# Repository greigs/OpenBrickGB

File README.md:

[For more info visit the hackaday writeup](https://hackaday.io/project/204088-lego-game-boy-functional-upgrade)

### Directory overview

- 3D Printed Parts: STL files for custom spacers and assemblies used inside the LEGO shell.
- Bill of Materials: CSVs listing components for the main PCB, button PCBs, and other parts.
- ButtonBoard PCBs: KiCad project assets and Gerbers for the button and D‑pad PCBs.
- Datasheets: Reference PDFs for key components (LCD, charger, amp, logic, regulators, etc.).
- Main PCB: KiCad project, fabrication outputs (Gerbers/DRLs), and pick‑and‑place (CPL) for the main board.
- Reference 3D Models: OBJ files used for fit checks and visualization of assemblies.
- Reference Bricklink Studio Designs: BrickLink Studio `.io` design files and a reference image for the LEGO build.

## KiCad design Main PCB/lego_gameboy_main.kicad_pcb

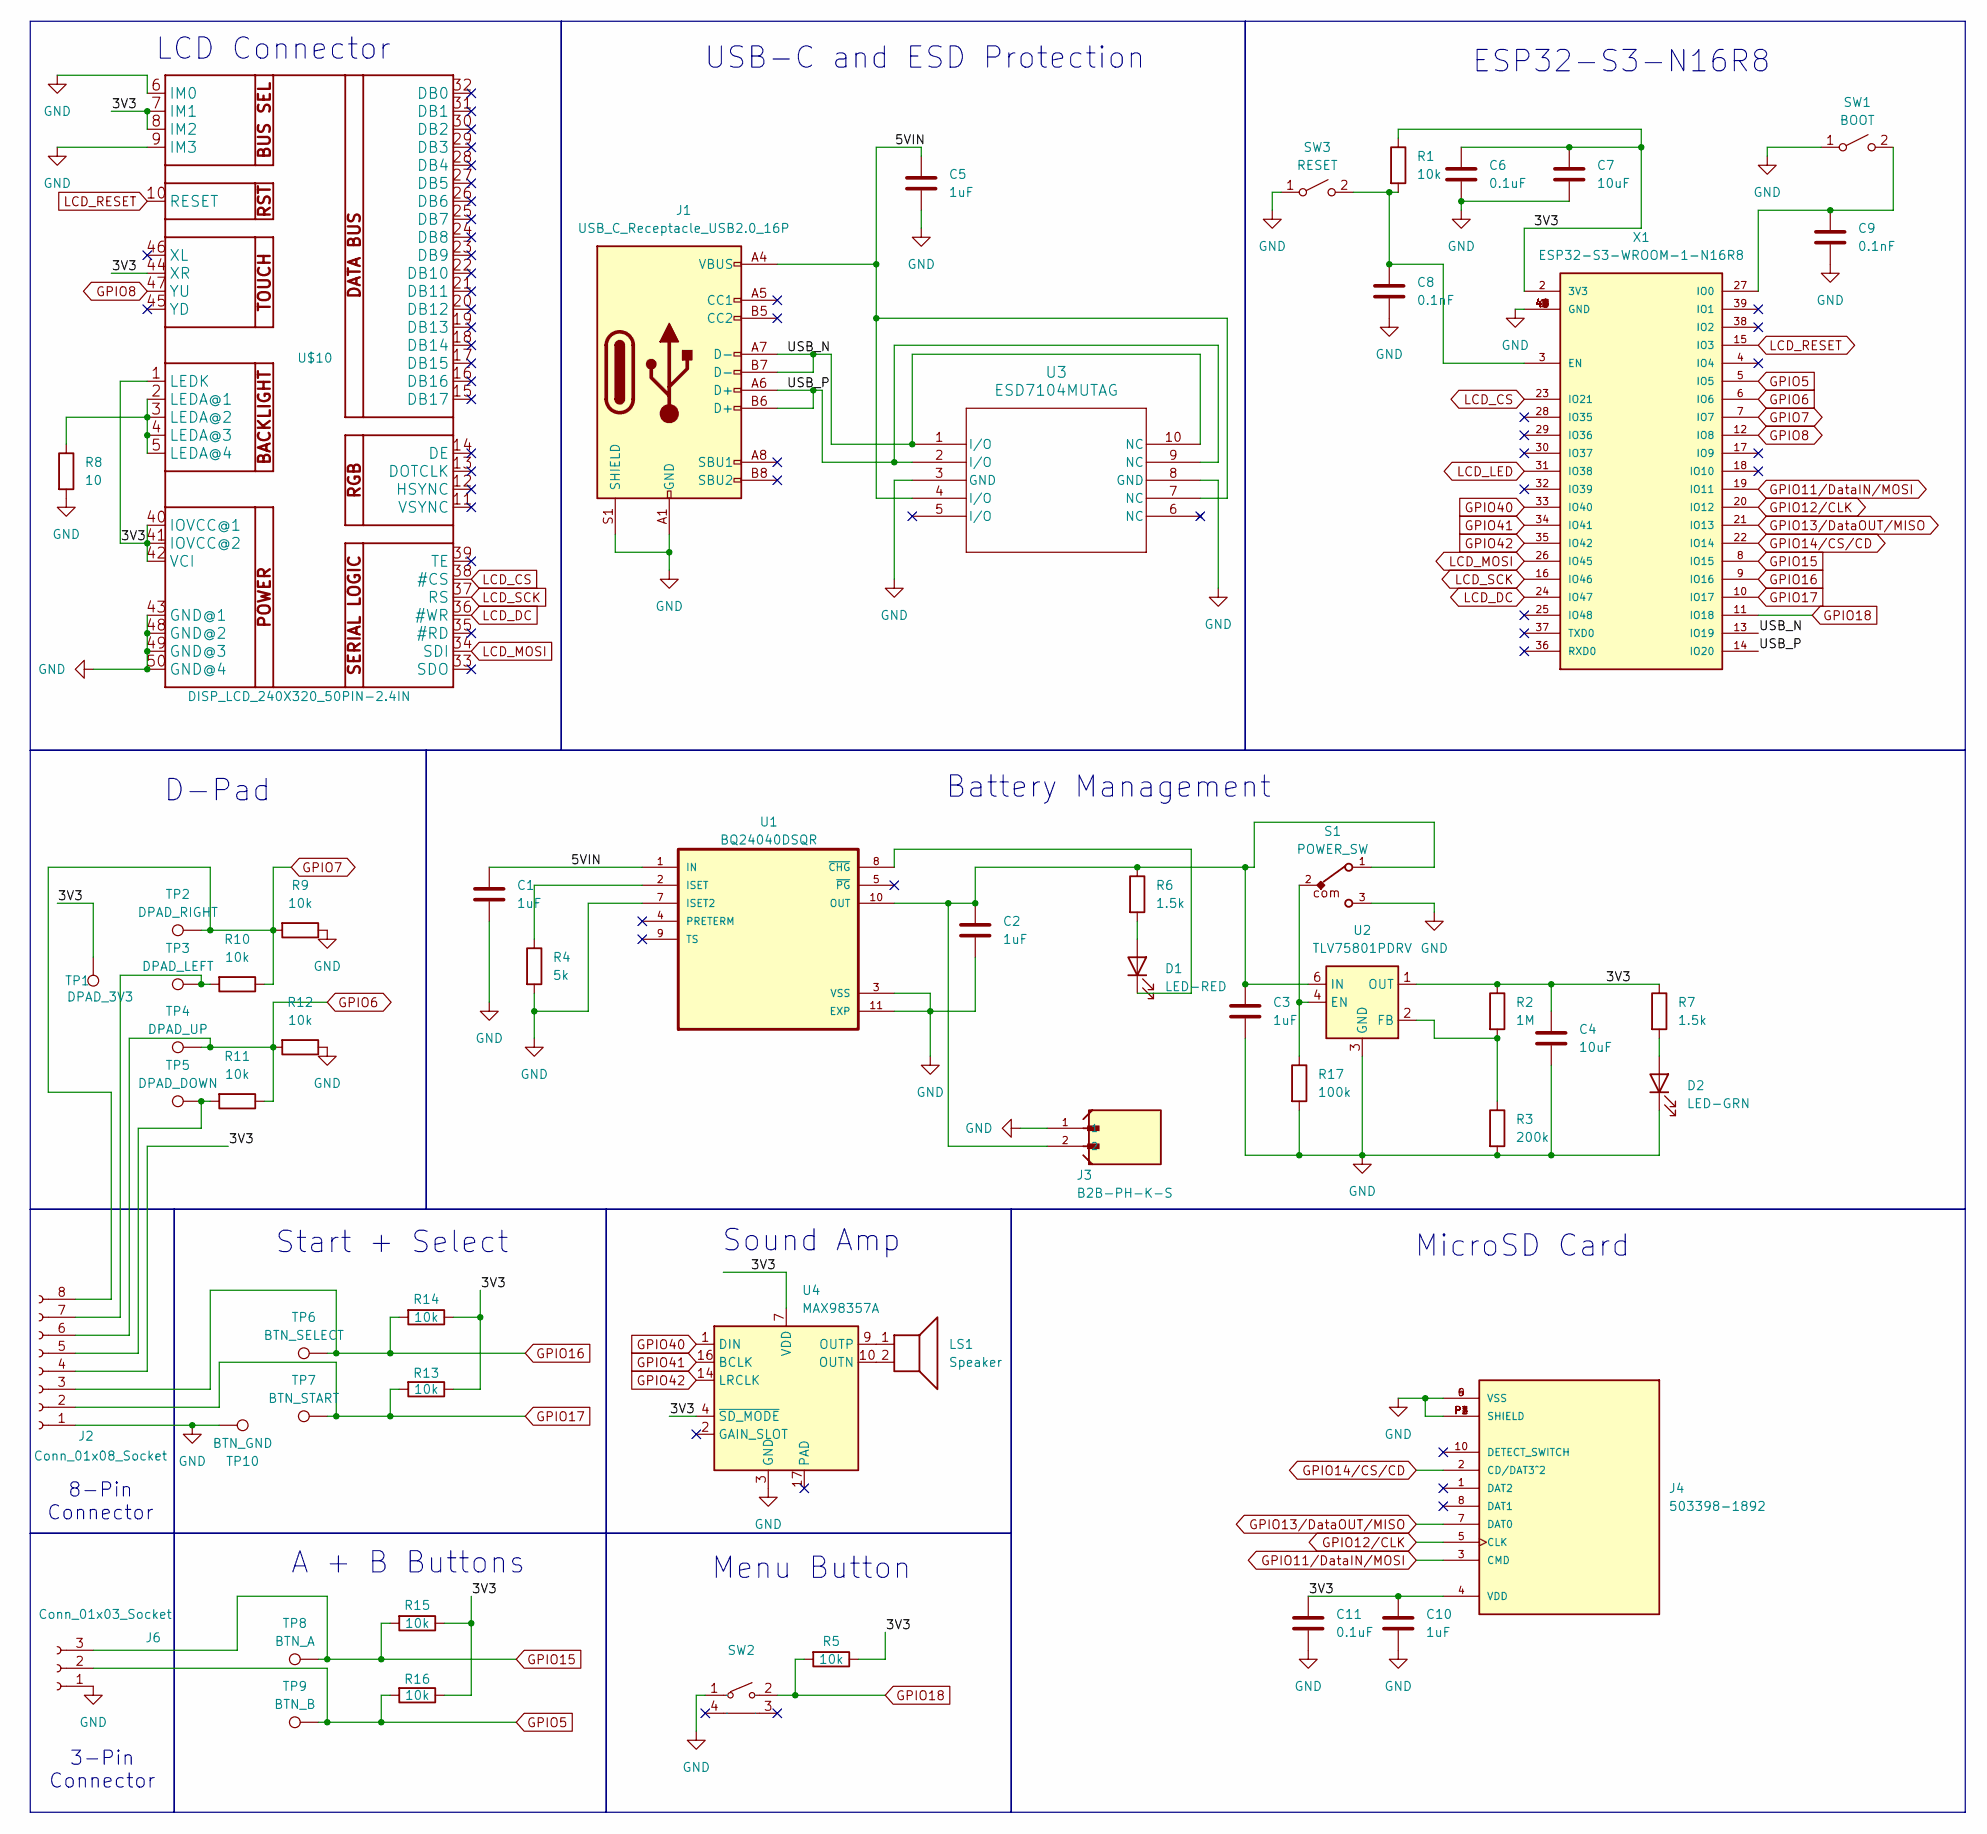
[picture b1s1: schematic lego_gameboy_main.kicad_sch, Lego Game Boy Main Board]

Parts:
C1, C2, C3, C5, C10: 1uF; C_0603_1608Metric
C4, C7: 10uF; C_0603_1608Metric
C6, C11: 0.1uF; C_0603_1608Metric
C8, C9: 0.1nF; C_0603_1608Metric
D1: LED-RED; LED_0603_1608Metric
D2: LED-GRN; LED_0603_1608Metric
J1: USB_C_Receptacle_USB2.0_16P; USB_C_Receptacle_G-Switch_GT-USB-7025
J2: Conn_01x08_Socket; JST_SUR_BM08B-SURS-TF_1x08-1MP_P0.80mm_Vertical
J3: B2B-PH-K-S; JST_PH_S2B-PH-K_1x02_P2.00mm_Horizontal
J4: 503398-1892; MOLEX_503398-1892; PARTREV 0; DigiKey_Part_Number WM11190CT-ND
J6: Conn_01x03_Socket; JST_SUR_BM03B-SURS-TF_1x03-1MP_P0.80mm_Vertical
LS1: Speaker; Speaker_CUI_CMR-1206S-67
R1, R5, R9, R10, R11, R12, R13, R14, R15, R16: 10k; R_0603_1608Metric
R2: 1M; R_0603_1608Metric
R3: 200k; R_0603_1608Metric
R4: 5k; R_0603_1608Metric
R6, R7: 1.5k; R_0603_1608Metric
R8: 10; R_0603_1608Metric
R17: 100k; R_0603_1608Metric
S1: POWER_SW; 450404015514
SW1: BOOT; SW_TS-1088-AR02016
SW2: SW-SMD_GT-TC185B-H038-L1; Manufacturer Part GT-TC185B-H038-L1; LCSC Part Name 4.9*5.5*3.8mm 卧贴 轻触开关
SW3: RESET; SW_TS-1088-AR02016
TP1: DPAD_3V3; TestPoint_Pad_D1.0mm
TP2: DPAD_RIGHT; TestPoint_Pad_D1.0mm
TP3: DPAD_LEFT; TestPoint_Pad_D1.0mm
TP4: DPAD_UP; TestPoint_Pad_D1.0mm
TP5: DPAD_DOWN; TestPoint_Pad_D1.0mm
TP6: BTN_SELECT; TestPoint_Pad_D1.0mm
TP7: BTN_START; TestPoint_Pad_D1.0mm
TP8: BTN_A; TestPoint_Pad_D1.0mm
TP9: BTN_B; TestPoint_Pad_D1.0mm
TP10: BTN_GND; TestPoint_Pad_D1.0mm
U1: BQ24040DSQR; SON40P200X200X80-11N
U2: TLV75801PDRV; WSON-6-1EP_2x2mm_P0.65mm_EP1x1.6mm
U3: ESD7104MUTAG; UDFN10_ONS
U4: MAX98357A; TQFN-16-1EP_3x3mm_P0.5mm_EP1.23x1.23mm
U$10: DISP_LCD_240X320_50PIN-2.4IN; TFT_2.4IN_240X320_50PIN
X1: ESP32-S3-WROOM-1-N16R8; ESP32S3WROOM1N8R2; MANUFACTURER_PART_NUMBER ESP32-S3-WROOM-1-N16R8

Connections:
/3V3: C4.1, C6.1, C7.1, C10.1, C11.1, J2.4, J4.4 (VDD), R1.1, R2.1, R5.1, R7.1, R13.1, R14.1, R15.1, R16.1, TP1.1, U2.1 (OUT), U4.4 (~SD_MODE), U4.7 (VDD), U4.8 (VDD), U$10.1 (LEDK), U$10.7 (IM1), U$10.8 (IM2), U$10.40 (IOVCC@1), U$10.41 (IOVCC@2), U$10.42 (VCI), U$10.44 (XR), X1.2 (3V3)
/5VIN: C1.1, C5.1, J1.A4 (VBUS), J1.A9 (VBUS), J1.B4 (VBUS), J1.B9 (VBUS), U1.1 (IN), U3.4 (I/O), U3.7 (NC)
/USB_N: J1.A7 (D-), J1.B7 (D-), U3.1 (I/O), U3.10 (NC), X1.13 (IO19)
/USB_P: J1.A6 (D+), J1.B6 (D+), U3.2 (I/O), U3.9 (NC), X1.14 (IO20)
GND: C1.2, C2.2, C3.2, C4.2, C5.2, C6.2, C7.2, C8.2, C9.2, C10.2, C11.2, D2.1 (K), J1.A1 (GND), J1.A12 (GND), J1.B1 (GND), J1.B12 (GND), J1.S1 (SHIELD), J2.1, J3.1, J4.6 (VSS), J4.9 (VSS), J4.P1 (SHIELD), J4.P2 (SHIELD), J4.P3 (SHIELD), J4.P4 (SHIELD), J6.1, R3.2, R4.2, R8.2, R9.1, R12.1, R17.2, S1.3, SW1.1 (A), SW2.1, SW3.1 (A), TP10.1, U1.3 (VSS), U1.7 (ISET2), U1.11 (EXP), U2.3 (GND), U2.7 (GND), U3.3 (GND), U3.8 (GND), U4.3 (GND), U4.11 (GND), U4.15 (GND), U$10.6 (IM0), U$10.9 (IM3), U$10.43 (GND@1), U$10.48 (GND@2), U$10.49 (GND@3), U$10.50 (GND@4), X1.1 (GND), X1.40 (GND), X1.41 (GND), X1.42 (GND), X1.43 (GND), X1.44 (GND), X1.45 (GND), X1.46 (GND), X1.47 (GND), X1.48 (GND), X1.49 (GND)
GPIO5: J6.2, R16.2, TP9.1, X1.5 (IO5)
GPIO6: J2.6, R11.1, R12.2, TP4.1, X1.6 (IO6)
GPIO7: J2.8, R9.2, R10.1, TP2.1, X1.7 (IO7)
GPIO8: U$10.47 (YU), X1.12 (IO8)
GPIO11/DataIN/MOSI: J4.3 (CMD), X1.19 (IO11)
GPIO12/CLK: J4.5 (CLK), X1.20 (IO12)
GPIO13/DataOUT/MISO: J4.7 (DAT0), X1.21 (IO13)
GPIO14/CS/CD: J4.2 (CD/DAT3^2), X1.22 (IO14)
GPIO15: J6.3, R15.2, TP8.1, X1.8 (IO15)
GPIO16: J2.3, R14.2, TP6.1, X1.9 (IO16)
GPIO17: J2.2, R13.2, TP7.1, X1.10 (IO17)
GPIO18: R5.2, SW2.2, X1.11 (IO18)
GPIO40: U4.1 (DIN), X1.33 (IO40)
GPIO41: U4.16 (BCLK), X1.34 (IO41)
GPIO42: U4.14 (LRCLK), X1.35 (IO42)
LCD_CS: U$10.38 (#CS), X1.23 (IO21)
LCD_DC: U$10.36 (#WR), X1.24 (IO47)
LCD_LED: X1.31 (IO38)
LCD_MOSI: U$10.34 (SDI), X1.26 (IO45)
LCD_RESET: U$10.10 (RESET), X1.15 (IO3)
LCD_SCK: U$10.37 (RS), X1.16 (IO46)
unnamed: D1.2 (A), R6.2
unnamed: D1.1 (K), U1.8 (~CHG)
unnamed: D2.2 (A), R7.2
unnamed: J2.5, R11.2, TP5.1
unnamed: J2.7, R10.2, TP3.1
unnamed: C9.1, SW1.2 (B), X1.27 (IO0)
unnamed: C8.1, R1.2, SW3.2 (B), X1.3 (EN)
unnamed: R4.1, U1.2 (ISET)
unnamed: C2.1, C3.1, J3.2, R6.1, S1.1, U1.10 (OUT), U2.6 (IN)
unnamed: R17.1, S1.2, U2.4 (EN)
unnamed: R2.2, R3.1, U2.2 (FB)
unnamed: LS1.2, U4.10 (OUTN)
unnamed: LS1.1, U4.9 (OUTP)
unnamed: R8.1, U$10.2 (LEDA@1), U$10.3 (LEDA@2), U$10.4 (LEDA@3), U$10.5 (LEDA@4)

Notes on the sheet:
Menu Button
Sound Amp
USB-C and ESD Protection
Battery Management
D-Pad
A + B Buttons
MicroSD Card
8-Pin Connector
Start + Select
3-Pin Connector
LCD Connector
ESP32-S3-N16R8

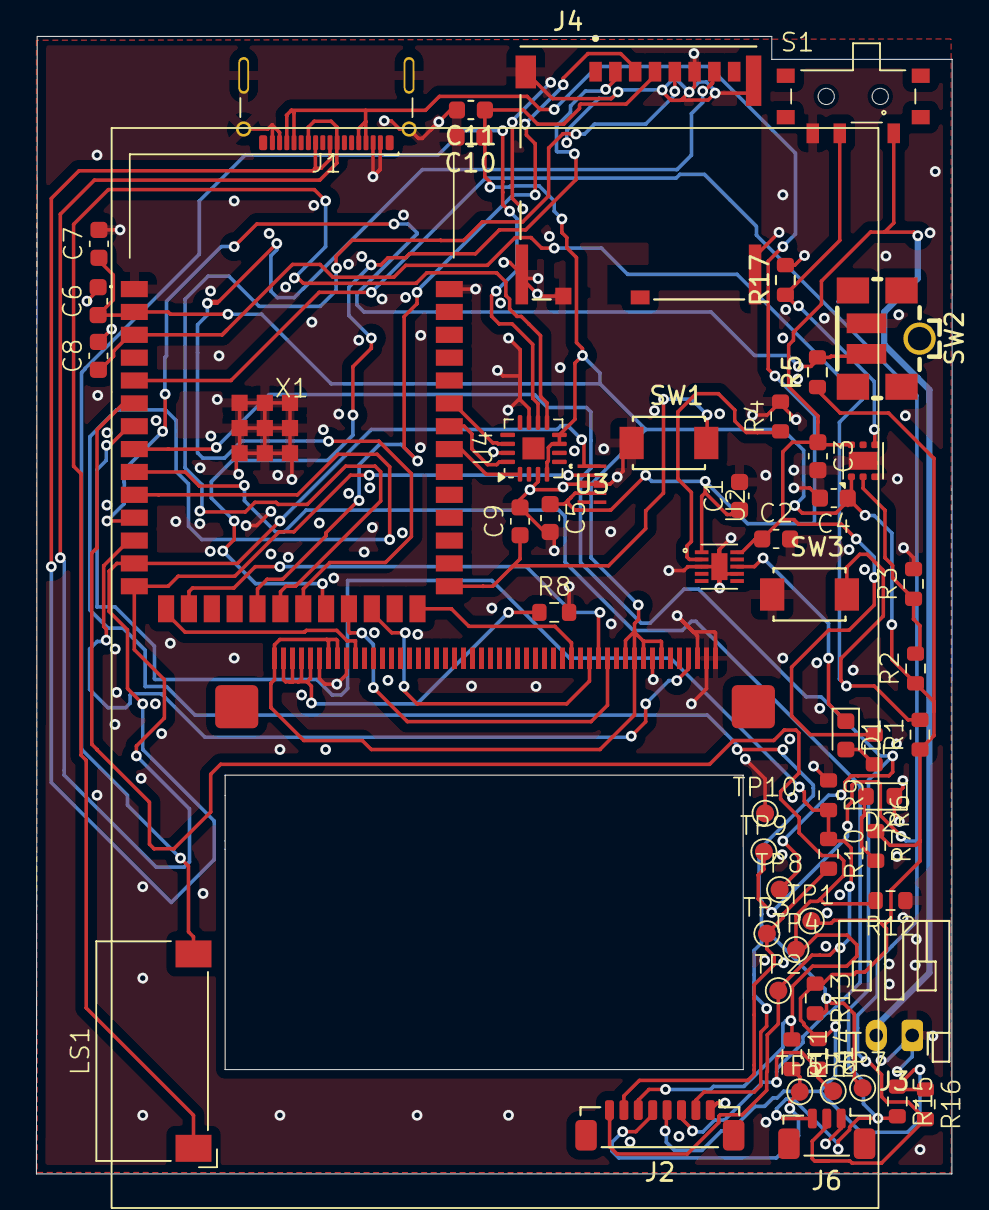
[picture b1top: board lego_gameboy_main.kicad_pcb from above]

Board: 4 copper layers, 50.9 x 63.2 mm, 56 parts (0 on the bottom side), 39 nets.

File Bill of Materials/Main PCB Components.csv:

Comment,Designator,Footprint,JLCPCB Part #,Purpose / Detail,Quantity
Conn_01x03_Socket,J6,Connector_JST:JST_SUR_BM03B-SURS-TF_1x03-1MP_P0.80mm_Vertical,C594379,Connector for A+B buttonboard,1
DISP_LCD_240X320_50PIN-2.4IN,U$10,Adafruit2.4inTFTBreakout:TFT_2.4IN_240X320_50PIN,C2828061,50-Pin LCD Connector,1
USB_C_Receptacle_USB2.0_16P,J1,Connector_USB:USB_C_Receptacle_G-Switch_GT-USB-7025,C963213,USB-C for power + flashing firmware,1
MAX98357A,U4,Package_DFN_QFN:TQFN-16-1EP_3x3mm_P0.5mm_EP1.23x1.23mm,C910544,Sound Amplifier,1
0.1uF,"C6,C11",Capacitor_SMD:C_0603_1608Metric,C14663,Passive,2
0.1nF,"C8,C9",Capacitor_SMD:C_0603_1608Metric,C14858,Passive,2
LED-RED,D1,LED_SMD:LED_0603_1608Metric,C2286,Battery Charge Indicator LED,1
LED-GRN,D2,LED_SMD:LED_0603_1608Metric,C2286,Power On Indicator LED,1
TLV75801PDRV,U2,Package_SON:WSON-6-1EP_2x2mm_P0.65mm_EP1x1.6mm,C2876308,Voltage Regulator,1
1.5k,"R6,R7",Resistor_SMD:R_0603_1608Metric,C22843,Passive,2
ESD7104MUTAG,U3,UDFN10_ONS,C328026,ESD Protection,1
B2B-PH-K-S,J3,Connector_JST:JST_PH_S2B-PH-K_1x02_P2.00mm_Horizontal,C157932,PH Battery Connector,1
10uF,"C4,C7",Capacitor_SMD:C_0603_1608Metric,C19702,Passive,2
POWER_SW,S1,450404015514:450404015514,C5446870,Power Slide Switch,1
BOOT,"SW3,SW1",TS-1088-AR02016:SW_TS-1088-AR02016,C720477,ESP32 Boot mode + Reset buttons,2
ESP32-S3-WROOM-1-N16R8,X1,ESP32:ESP32S3WROOM1N8R2,C2913202,Main SoC,1
200k,R3,Resistor_SMD:R_0603_1608Metric,C25811,Passive,1
10,R8,Resistor_SMD:R_0603_1608Metric,C22859,Passive,1
5k,R4,Resistor_SMD:R_0603_1608Metric,C2828621,Passive,1
503398-1892,J4,MOLEX_503398-1892:MOLEX_503398-1892,C428492,Passive,1
~,SW2,ProLib_pcs_2025-10-09:SW-SMD_GT-TC185B-H038-L1,C778160,Menu Button,1
1M,R2,Resistor_SMD:R_0603_1608Metric,C22935,Passive,1
1uF,"C1,C2,C3,C5,C10",Capacitor_SMD:C_0603_1608Metric,C15849,Passive,5
BQ24040DSQR,U1,BQ24040DSQR:SON40P200X200X80-11N,C81080,Battery Management,1
10k,"R1,R5,R9,R10,R11,R12,R13,R14,R15,R16",Resistor_SMD:R_0603_1608Metric,C25804,Passive,10
100k,R17,Resistor_SMD:R_0603_1608Metric,C25803,Passive,1
Conn_01x08_Socket,J2,Connector_JST:JST_SUR_BM08B-SURS-TF_1x08-1MP_P0.80mm_Vertical,C5143489,Connector for select + start + D-pad boards,1

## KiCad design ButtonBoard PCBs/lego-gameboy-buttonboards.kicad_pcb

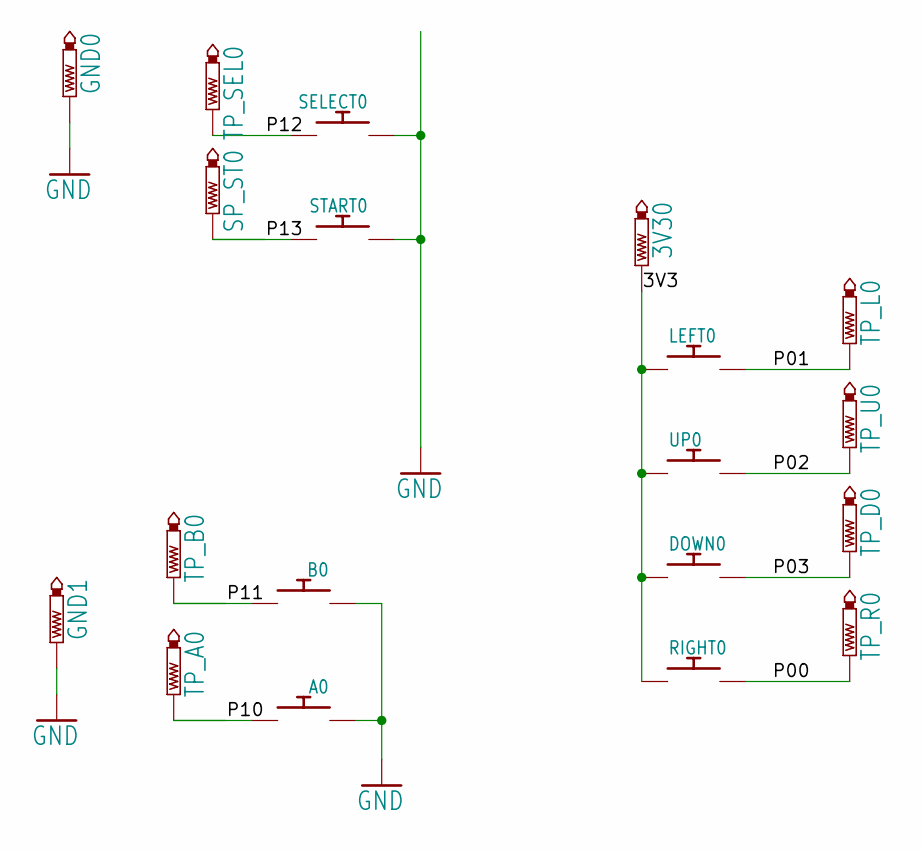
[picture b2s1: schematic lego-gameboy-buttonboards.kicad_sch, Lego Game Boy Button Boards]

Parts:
3V30: PTR1TP20R; TP20R
A0: DMG-BTN; DMG_BTN1
B0: DMG-BTN; DMG_BTN1
DOWN0: DMG-BTN; DMG_BTN1
GND0, GND1: PTR1TP20R; TP20R
LEFT0: DMG-BTN; DMG_BTN1
RIGHT0: DMG-BTN; DMG_BTN1
SELECT0: DMG-BTN; DMG_BTN2_TACT2
SP_ST0: PTR1TP20R; TP20R
START0: DMG-BTN; DMG_BTN2_TACT2
TP_A0: PTR1TP20R; TP20R
TP_B0: PTR1TP20R; TP20R
TP_D0: PTR1TP20R; TP20R
TP_L0: PTR1TP20R; TP20R
TP_R0: PTR1TP20R; TP20R
TP_SEL0: PTR1TP20R; TP20R
TP_U0: PTR1TP20R; TP20R
UP0: DMG-BTN; DMG_BTN1

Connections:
/3V3: 3V30.TP, DOWN0.P$2, LEFT0.P$2, RIGHT0.P$2, UP0.P$2
/P00: RIGHT0.P$1, TP_R0.TP
/P01: LEFT0.P$1, TP_L0.TP
/P02: TP_U0.TP, UP0.P$1
/P03: DOWN0.P$1, TP_D0.TP
/P10: A0.P$1, TP_A0.TP
/P11: B0.P$1, TP_B0.TP
/P12: SELECT0.P$2, TP_SEL0.TP; also elsewhere on the board
/P13: SP_ST0.TP, START0.P$2; also elsewhere on the board
GND: A0.P$2, B0.P$2, GND0.TP, GND1.TP, SELECT0.P$1, START0.P$1; also elsewhere on the board

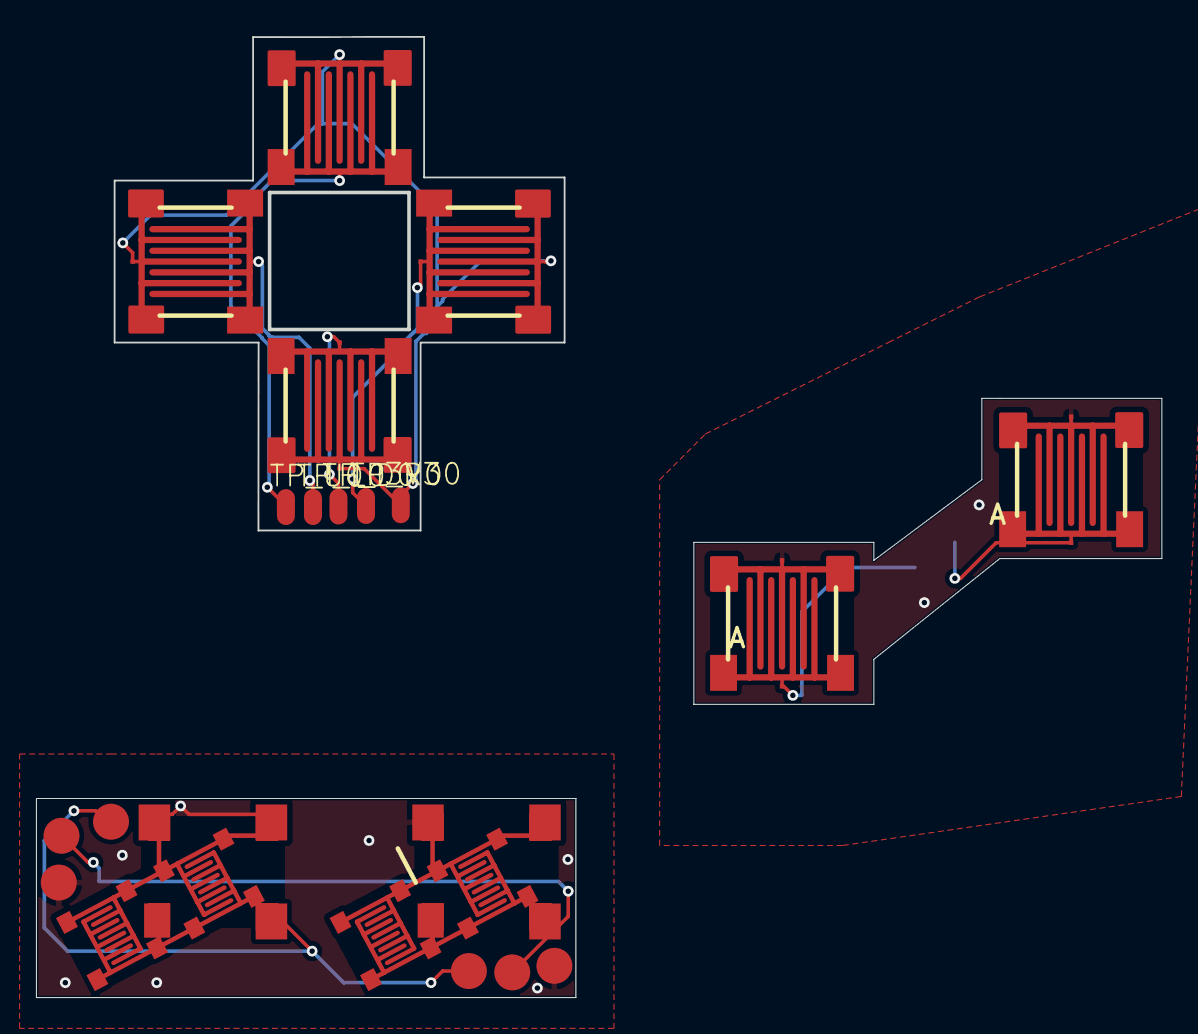
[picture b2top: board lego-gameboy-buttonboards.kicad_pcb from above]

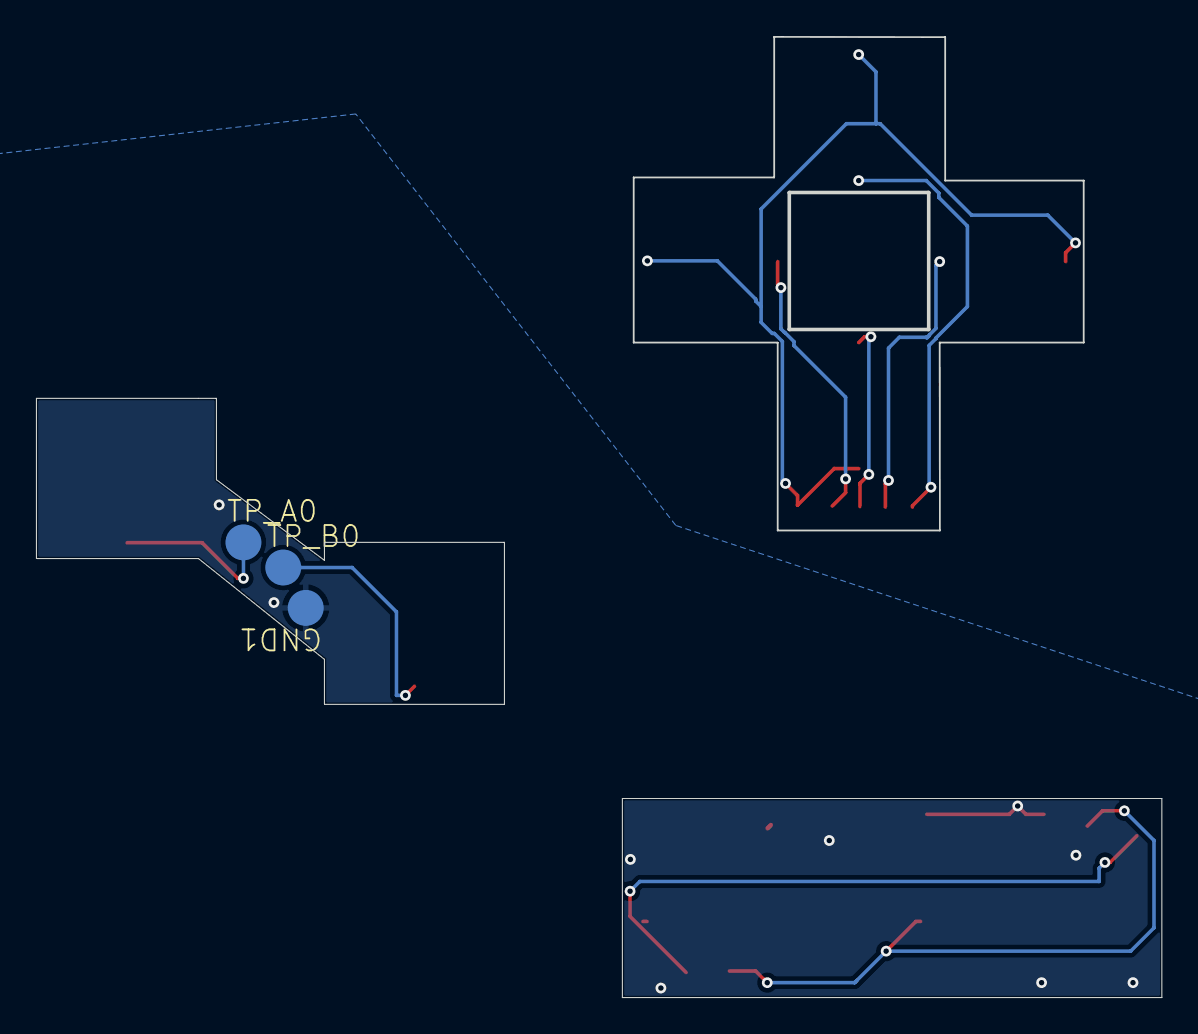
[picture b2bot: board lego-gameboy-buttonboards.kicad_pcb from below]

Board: 2 copper layers, 62.5 x 53.4 mm, 22 parts (3 on the bottom side), 10 nets.

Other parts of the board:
GND0#2: PTR1TP20R; TP20R
SP_ST0#2: PTR1TP20R; TP20R
TP_SEL0#2: PTR1TP20R; TP20R

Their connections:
/P12: TP_SEL0#2.TP; also elsewhere on the board
/P13: SP_ST0#2.TP; also elsewhere on the board
GND: GND0#2.TP; also elsewhere on the board

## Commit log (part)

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2025-10-12 v1 design cleaned up
2025-10-12 add readme
2025-10-12 updated BOM
2025-10-12 update links
2025-10-12 added every other component needed
2026-01-07 moved usb-c to top edge
2026-03-07 added instructions document for top part
2026-06-02 3d printable files from v1 of the kit
